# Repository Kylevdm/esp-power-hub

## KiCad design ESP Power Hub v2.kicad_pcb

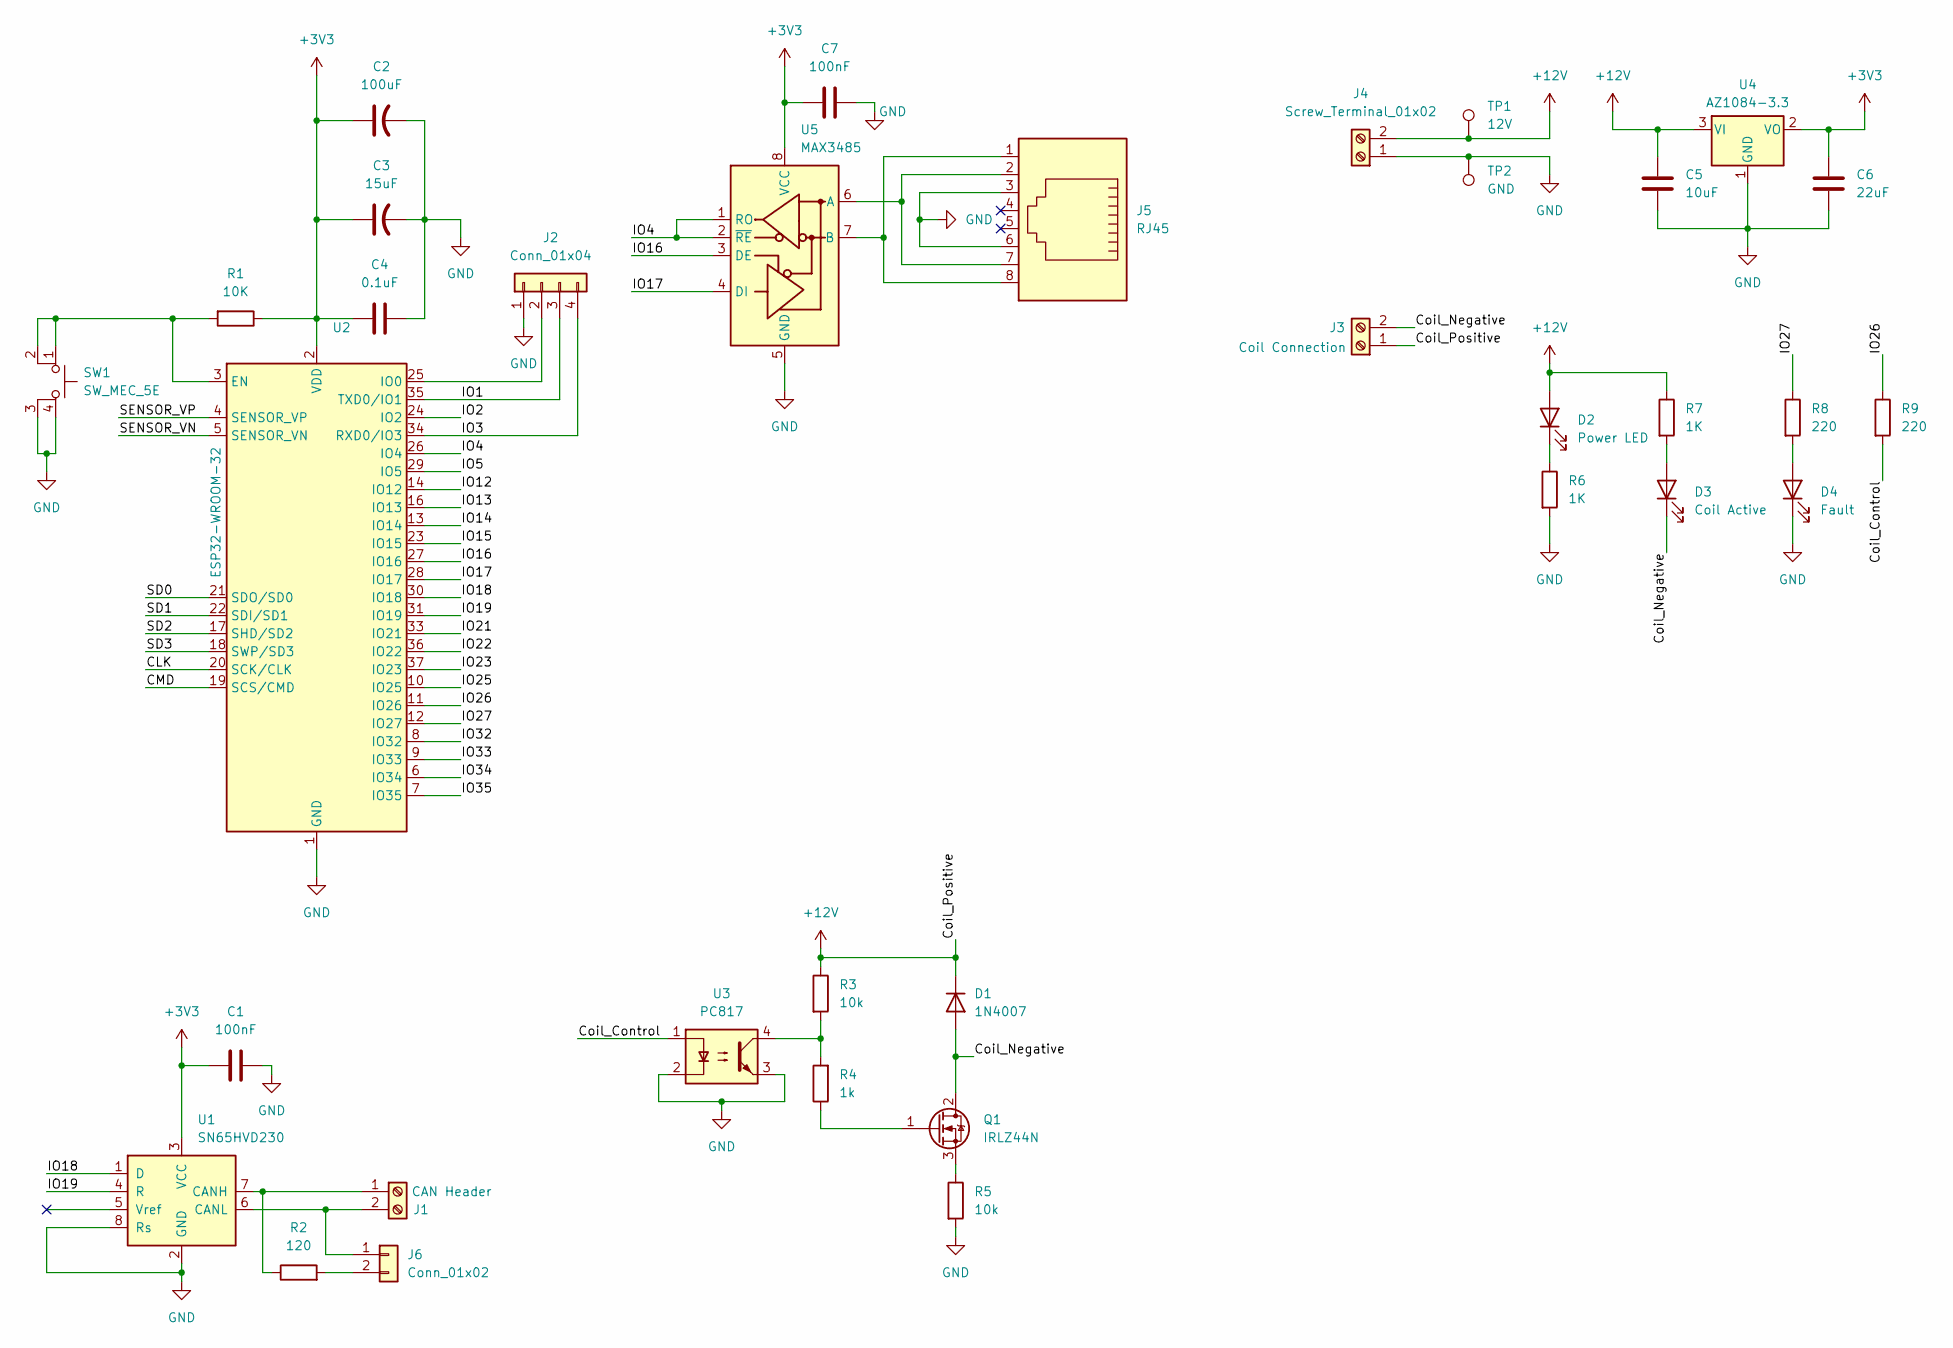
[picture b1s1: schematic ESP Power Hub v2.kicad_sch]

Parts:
C1, C7: 100nF; C_0603_1608Metric
C2: 100uF; C_Radial_D5.0mm_H7.0mm_P2.00mm
C3: 15uF; C_Radial_D4.0mm_H5.0mm_P1.50mm
C4: 0.1uF; C_0603_1608Metric
C5: 10uF; C_0603_1608Metric
C6: 22uF; C_0603_1608Metric
D1: 1N4007; D_DO-41_SOD81_P10.16mm_Horizontal
D2: Power LED; LED_D5.0mm
D3: Coil Active; LED_D5.0mm
D4: Fault; LED_D5.0mm
J1: CAN Header; TerminalBlock_MaiXu_MX126-5.0-02P_1x02_P5.00mm
J2: Conn_01x04; PinHeader_1x04_P2.54mm_Vertical
J3: Coil Connection; TerminalBlock_MaiXu_MX126-5.0-02P_1x02_P5.00mm
J4: Screw_Terminal_01x02; TerminalBlock_MaiXu_MX126-5.0-02P_1x02_P5.00mm
J5: RJ45; RJ45_Amphenol_54602-x08_Horizontal
J6: Conn_01x02; PinSocket_1x02_P2.54mm_Vertical
Q1: IRLZ44N; TO-220-3_Vertical
R1: 10K; R_0603_1608Metric
R2: 120; R_0603_1608Metric
R3, R5: 10k; R_0805_2012Metric
R4: 1k; R_0805_2012Metric
R6, R7: 1K; R_0603_1608Metric
R8, R9: 220; R_0603_1608Metric
SW1: SW_MEC_5E; SW_MEC_5GSH9
TP1: 12V; TestPoint_THTPad_D2.0mm_Drill1.0mm
TP2: GND; TestPoint_THTPad_D2.0mm_Drill1.0mm
U1: SN65HVD230; SOIC-8_3.9x4.9mm_P1.27mm
U2: ESP32-WROOM-32
U3: PC817; DIP-4_W7.62mm
U4: AZ1084-3.3; TO-252-2
U5: MAX3485; SOIC-8_3.9x4.9mm_P1.27mm

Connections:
+3V3: C1.2, C2.1, C3.1, C4.1, C6.1, C7.2, R1.1, U1.3 (VCC), U2.2 (VDD), U4.2 (VO), U5.8 (VCC)
+12V: C5.1, D1.1 (K), D2.2 (A), J3.1, J4.2, R3.1, R7.1, TP1.1, U4.3 (VI)
/CLK: U2.20 (SCK/CLK)
/CMD: U2.19 (SCS/CMD)
/Coil_Control: R9.2, U3.1
/Coil_Negative: D1.2 (A), D3.1 (K), J3.2, Q1.2 (D)
/IO1: J2.3, U2.35 (TXD0/IO1)
/IO2: U2.24 (IO2)
/IO3: J2.4, U2.34 (RXD0/IO3)
/IO4: U2.26 (IO4), U5.1 (RO), U5.2 (~RE)
/IO5: U2.29 (IO5)
/IO12: U2.14 (IO12)
/IO13: U2.16 (IO13)
/IO14: U2.13 (IO14)
/IO15: U2.23 (IO15)
/IO16: U2.27 (IO16), U5.3 (DE)
/IO17: U2.28 (IO17), U5.4 (DI)
/IO18: U1.1 (D), U2.30 (IO18)
/IO19: U1.4 (R), U2.31 (IO19)
/IO21: U2.33 (IO21)
/IO22: U2.36 (IO22)
/IO23: U2.37 (IO23)
/IO25: U2.10 (IO25)
/IO26: R9.1, U2.11 (IO26)
/IO27: R8.1, U2.12 (IO27)
/IO32: U2.8 (IO32)
/IO33: U2.9 (IO33)
/IO34: U2.6 (IO34)
/IO35: U2.7 (IO35)
/SD0: U2.21 (SDO/SD0)
/SD1: U2.22 (SDI/SD1)
/SD2: U2.17 (SHD/SD2)
/SD3: U2.18 (SWP/SD3)
/SENSOR_VN: U2.5 (SENSOR_VN)
/SENSOR_VP: U2.4 (SENSOR_VP)
GND: C1.1, C2.2, C3.2, C4.2, C5.2, C6.2, C7.1, D4.1 (K), J2.1, J4.1, J5.3, J5.6, R5.2, R6.2, SW1.3 (K), SW1.4 (A), TP2.1, U1.2 (GND), U1.8 (Rs), U2.1 (GND), U2.15 (GND), U2.38 (GND), U2.39 (GND), U3.2, U3.3, U4.1 (GND), U5.5 (GND)
unnamed: D2.1 (K), R6.1
unnamed: D3.2 (A), R7.2
unnamed: D4.2 (A), R8.2
unnamed: J1.1, R2.1, U1.7 (CANH)
unnamed: J1.2, J6.1, U1.6 (CANL)
unnamed: J2.2, U2.25 (IO0)
unnamed: J6.2, R2.2
unnamed: Q1.1 (G), R4.1
unnamed: Q1.3 (S), R5.1
unnamed: R3.2, R4.2, U3.4
unnamed: R1.2, SW1.1, SW1.2, U2.3 (EN)
unnamed: J5.2, J5.7, U5.6 (A)
unnamed: J5.1, J5.8, U5.7 (B)

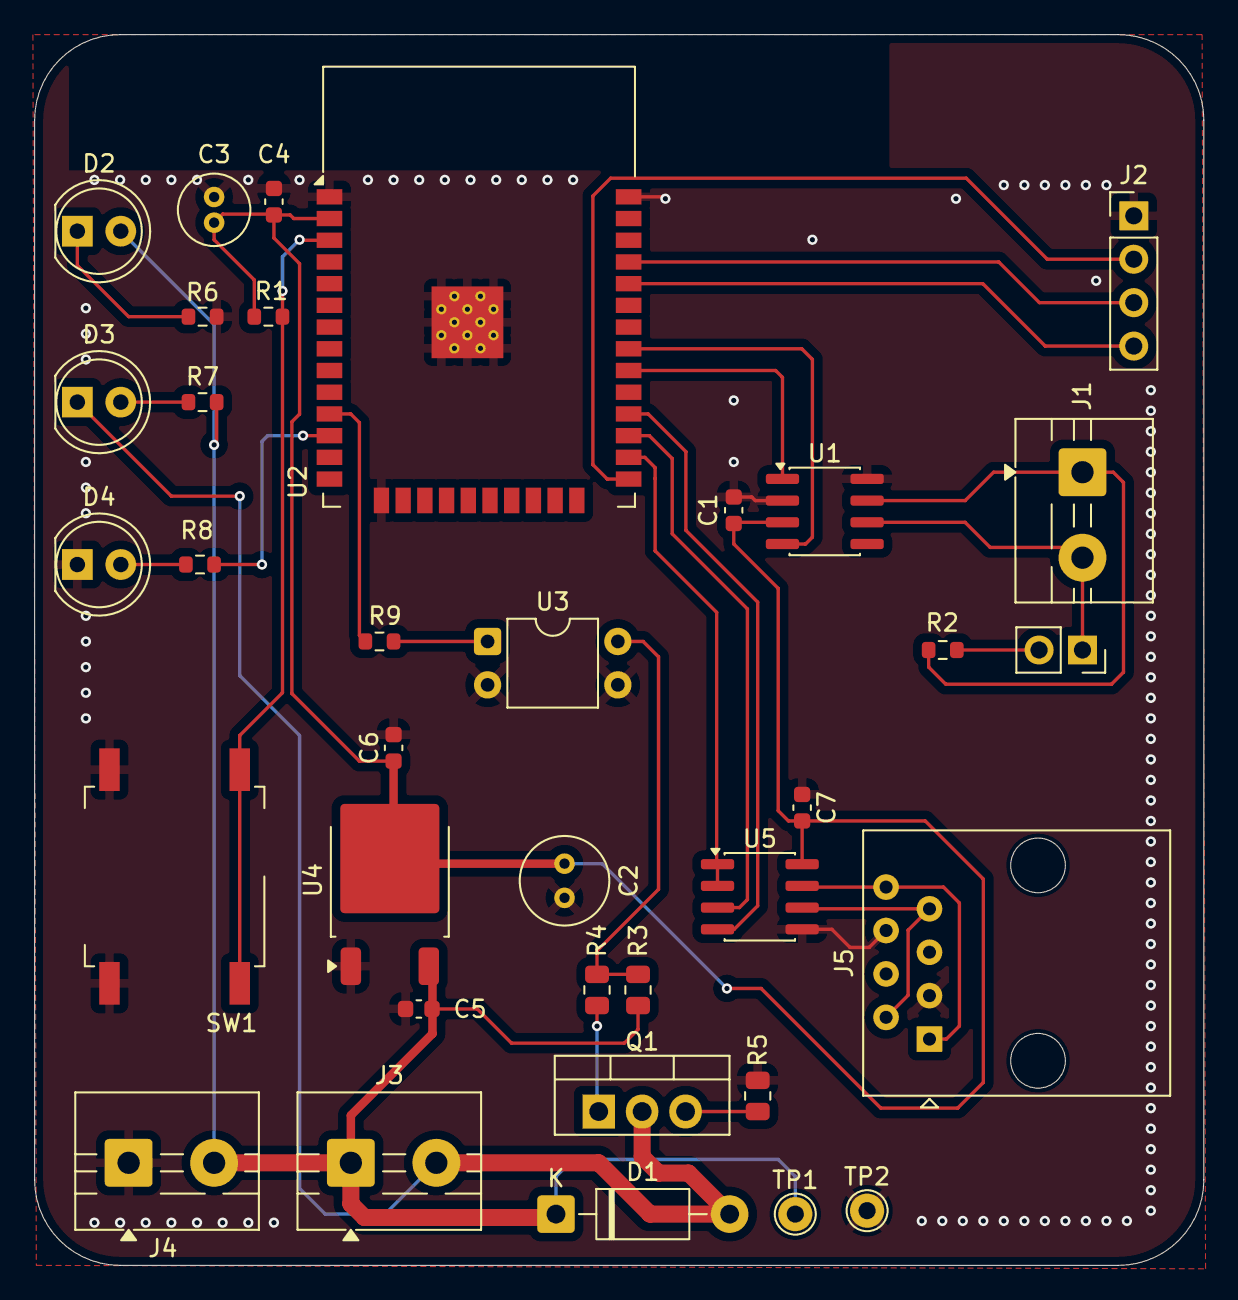
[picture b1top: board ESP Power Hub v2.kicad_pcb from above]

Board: 2 copper layers, 68.4 x 72.0 mm, 35 parts (0 on the bottom side), 27 nets.

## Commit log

2026-02-04 Add files via upload
    Initial design upload
2026-06-03 Add ESPHome firmware for T-CAN485 with charge controller
    Phase 1 firmware for the ESP Power Hub using a LilyGo T-CAN485 dev board:
    - Main ESPHome config with T-CAN485 pin mapping (CAN, RS485, relay, LED)
    - Seplos V3 BMS integration via modbus_controller with reusable pack template
    - Emerson/Vertiv R48-3000e3 rectifier via existing external component
    - Custom charge_controller component with:
    - Autonomous charging state machine (STANDBY/BULK/ABSORB/FLOAT/ALARM)
2026-06-03 Add CLAUDE.md and gitignore updates
    Add project documentation for future Claude Code sessions and ignore
    __pycache__ directories and firmware-specific secrets/build artifacts.
    https://claude.ai/code/session_011SFWcxyuFjZCRARbZNHVyz
2026-06-04 Fix 6 bugs found in code review of charge controller
    1. ALARM state was inescapable: loop() gated update_state_machine_()
    behind state != ALARM, but the only ALARM exit path lived inside
    that function. Removed the gate so the ALARM case can run.
    2. Charging never started when SOC >= rebulk_soc: STANDBY only
    transitioned to BULK when SOC < threshold. Added STANDBY->FLOAT
    path for batteries already above rebulk threshold.
